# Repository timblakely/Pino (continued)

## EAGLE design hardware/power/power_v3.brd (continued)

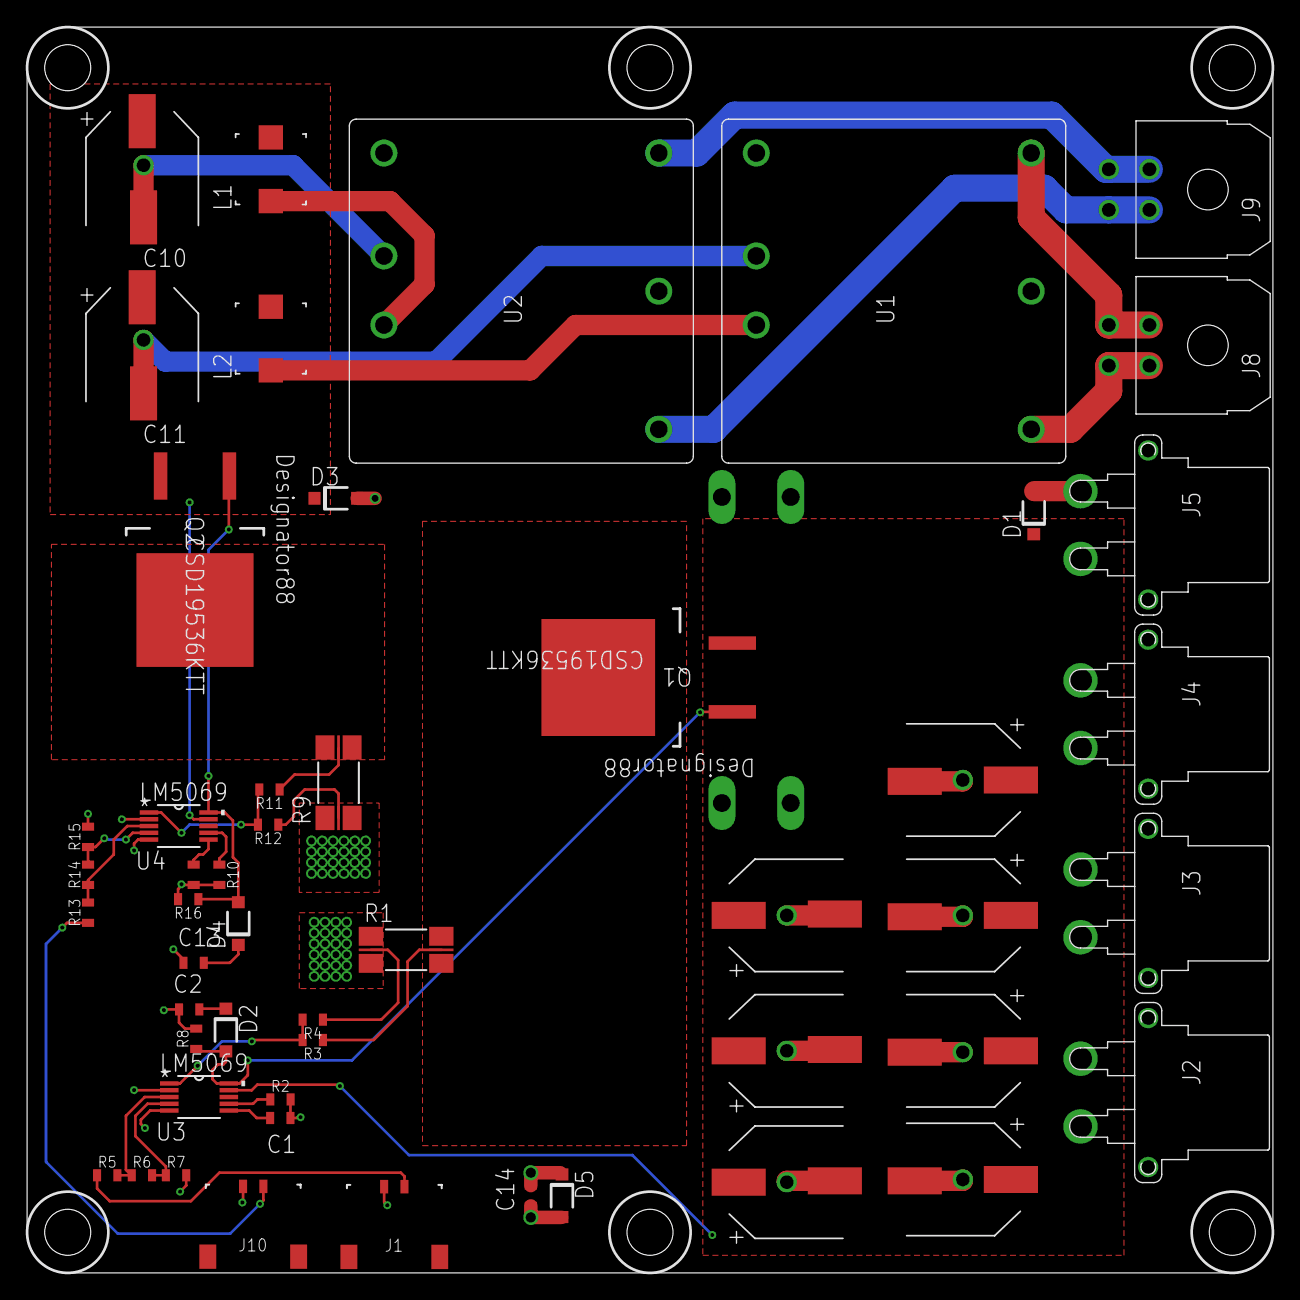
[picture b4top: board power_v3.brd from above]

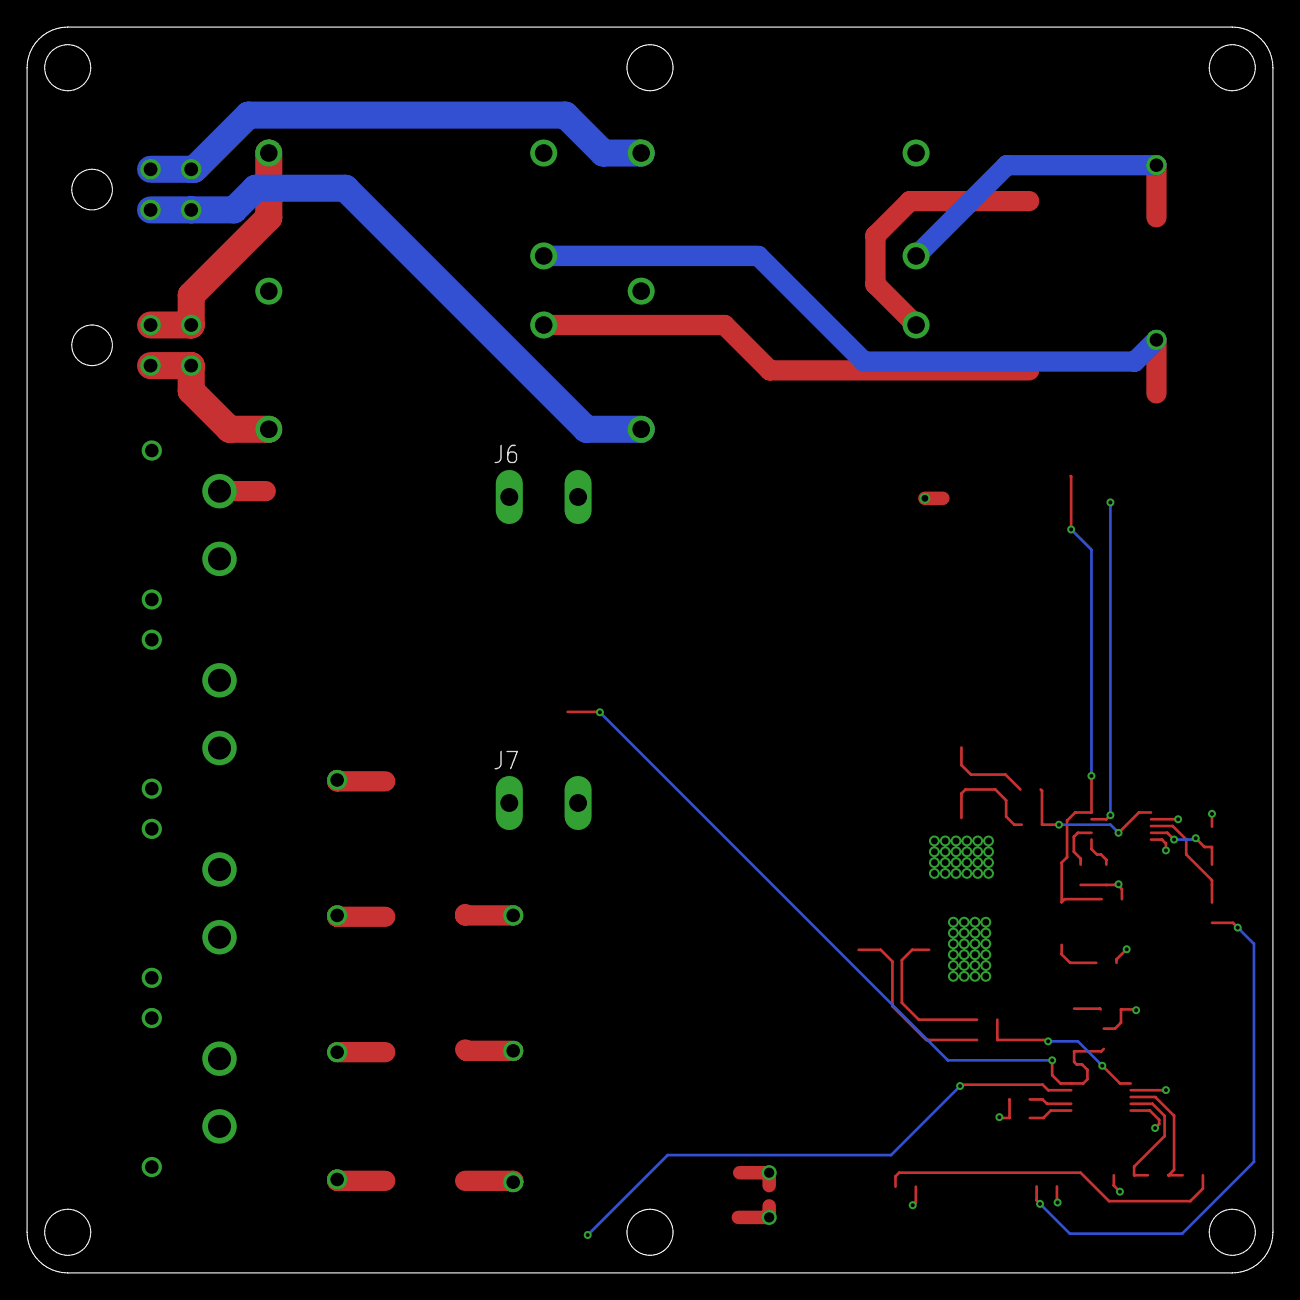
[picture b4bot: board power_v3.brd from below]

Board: 4 copper layers, 92.0 x 92.0 mm, 53 parts (2 on the bottom side), 32 nets.

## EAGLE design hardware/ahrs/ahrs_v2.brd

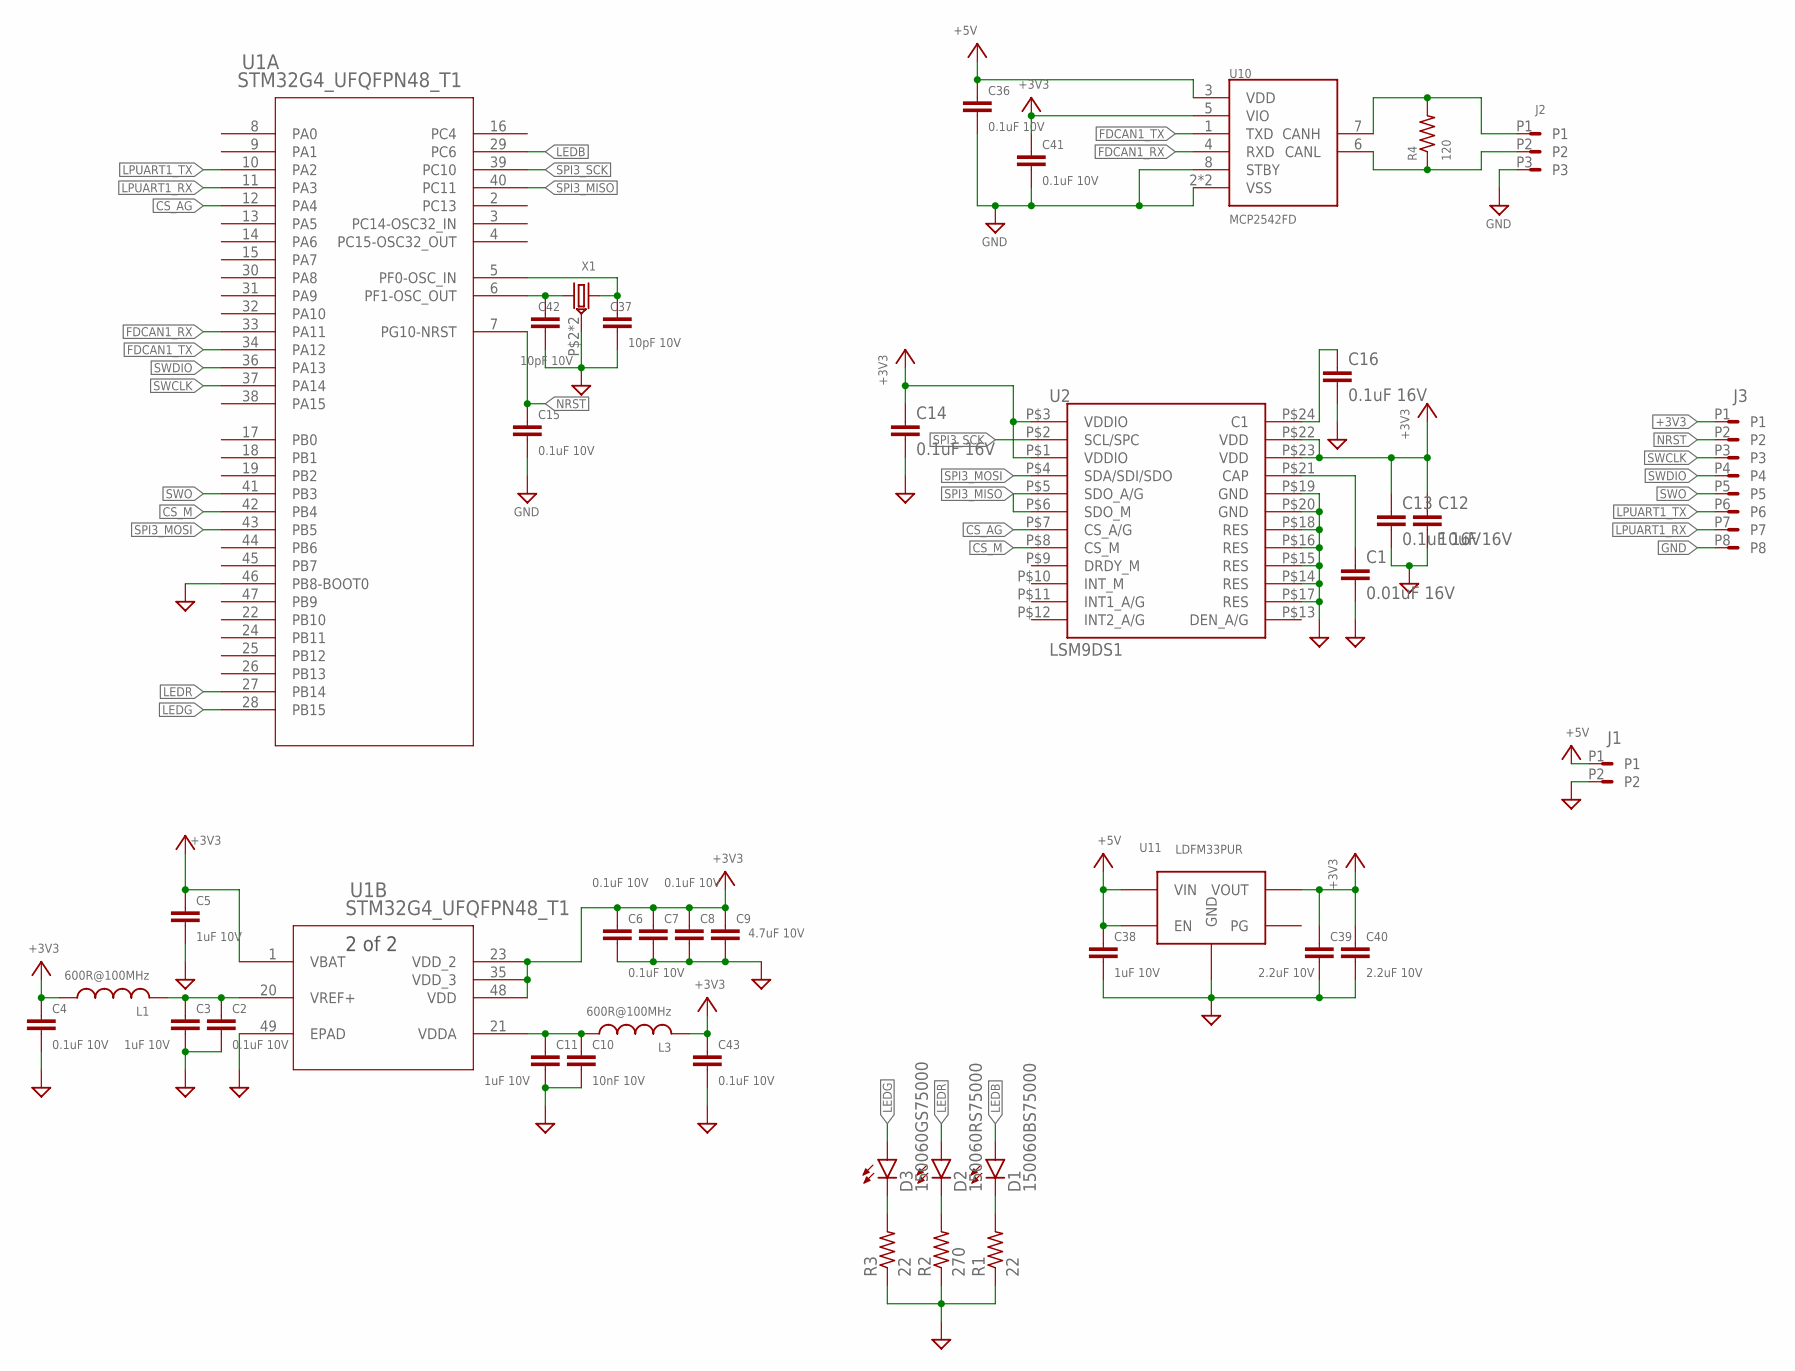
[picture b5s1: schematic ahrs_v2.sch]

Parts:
C1: 0.01uF 16V; C0603
C2, C4, C6, C7, C8, C15, C36, C41, C43: 0.1uF 10V; C0603
C3, C5, C11, C38: 1uF 10V; C0603
C9: 4.7uF 10V; C0603
C10: 10nF 10V; C0603
C12: 10uF 16V; C0603
C13, C14, C16: 0.1uF 16V; C0603
C37, C42: 10pF 10V; C0603
C39, C40: 2.2uF 10V; C0603
D1: 150060BS75000; D0603
D2: 150060RS75000; D0603
D3: 150060GS75000; D0603
J1: LINEAR_2_5040500291; MOLEX_5040500291
J2: LINEAR_35040500391; MOLEX_5040500391
J3: LINEAR_85040500891; MOLEX_5040500891
L1, L3: 600R@100MHz; L0603
R1, R3: 22; R0603
R2: 270; R0603
R4: 120; R0603
U1: STM32G4_UFQFPN48_T1; UFQFPN-48_7X7X0P55MM
U2: LSM9DS1; LGA24_3.5X3X1
U10: MCP2542FD; TDFN_2X3
U11: LDFM33PUR; DFN6_2X2
X1: CRYSTAL_NX2016SA-24MHZ-EXS00A-CS11335; NX201SA

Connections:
+3V3: C4.1, C5.1, C6.1, C7.1, C8.1, C9.1, C12.1, C13.1, C14.1, C39.1, C40.1, C41.1, C43.1, J3.P1, L1.1, L3.2, U1.1 (VBAT), U1.23 (VDD_2), U1.35 (VDD_3), U1.48 (VDD), U2.P$1 (VDDIO), U2.P$3 (VDDIO), U2.P$22 (VDD), U2.P$23 (VDD), U10.5 (VIO), U11.PIN1 (VOUT)
+5V: C36.1, C38.1, J1.P1, U10.3 (VDD), U11.PIN5 (EN), U11.PIN6 (VIN); also elsewhere on the board
CS_AG: U1.12 (PA4), U2.P$7 (CS_A/G)
CS_M: U1.42 (PB4), U2.P$8 (CS_M)
FDCAN1_RX: U1.33 (PA11), U10.4 (RXD)
FDCAN1_TX: U1.34 (PA12), U10.1 (TXD)
GND: C1.2, C2.2, C3.2, C4.2, C5.2, C6.2, C7.2, C8.2, C9.2, C10.2, C11.2, C12.2, C13.2, C14.2, C15.2, C16.2, C36.2, C37.2, C38.2, C39.2, C40.2, C41.2, C42.2, C43.2, J1.P2, J2.P3, J3.P8, R1.1, R2.1, R3.1, U1.46 (PB8-BOOT0), U1.49 (EPAD), U2.P$14 (RES), U2.P$15 (RES), U2.P$16 (RES), U2.P$17 (RES), U2.P$18 (RES), U2.P$19 (GND), U2.P$20 (GND), U10.2 (VSS), U10.8 (STBY), U10.PAD (VSS), U11.PAD (GND), U11.PIN4 (GND), X1.P$2 (GND), X1.P$4 (GND); also elsewhere on the board
LEDB: D1.2 (A), U1.29 (PC6)
LEDG: D3.2 (A), U1.28 (PB15)
LEDR: D2.2 (A), U1.27 (PB14)
LPUART1_RX: J3.P7, U1.11 (PA3)
LPUART1_TX: J3.P6, U1.10 (PA2)
unnamed: C2.1, C3.1, L1.2, U1.20 (VREF+)
unnamed: C37.1, U1.5 (PF0-OSC_IN), X1.P$3 (2)
unnamed: C42.1, U1.6 (PF1-OSC_OUT), X1.P$1 (1)
unnamed: C1.1, U2.P$21 (CAP)
unnamed: C16.1, U2.P$24 (C1)
unnamed: D3.1 (C), R3.2
unnamed: D2.1 (C), R2.2
unnamed: D1.1 (C), R1.2
unnamed: J2.P1, R4.2, U10.7 (CANH)
unnamed: J2.P2, R4.1, U10.6 (CANL)
unnamed: C10.1, C11.1, L3.1, U1.21 (VDDA)
NRST: C15.1, J3.P2, U1.7 (PG10-NRST)
SPI3_MISO: U1.40 (PC11), U2.P$5 (SDO_A/G), U2.P$6 (SDO_M)
SPI3_MOSI: U1.43 (PB5), U2.P$4 (SDA/SDI/SDO)
SPI3_SCK: U1.39 (PC10), U2.P$2 (SCL/SPC)
SWCLK: J3.P3, U1.37 (PA14)
SWDIO: J3.P4, U1.36 (PA13)
SWO: J3.P5, U1.41 (PB3)

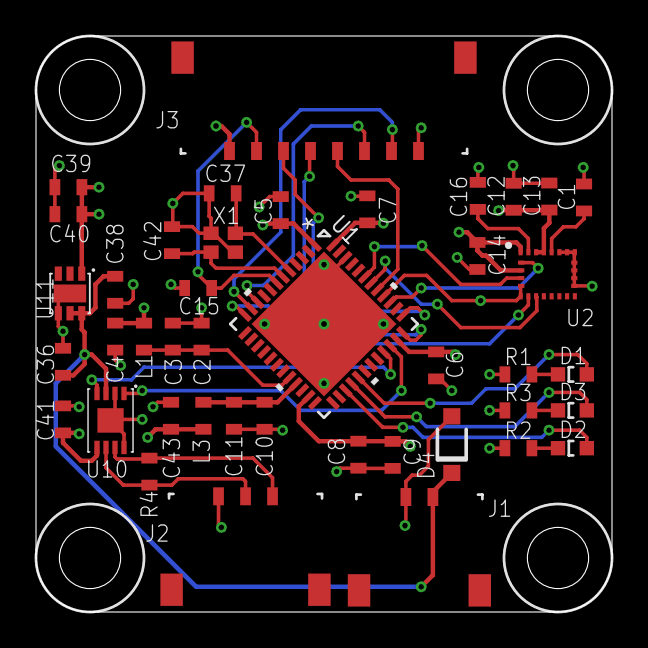
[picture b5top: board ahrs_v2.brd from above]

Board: 4 copper layers, 32.0 x 32.0 mm, 42 parts (0 on the bottom side), 30 nets.

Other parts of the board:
D4: SOD123

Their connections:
+5V: D4.C; also elsewhere on the board
GND: D4.A; also elsewhere on the board

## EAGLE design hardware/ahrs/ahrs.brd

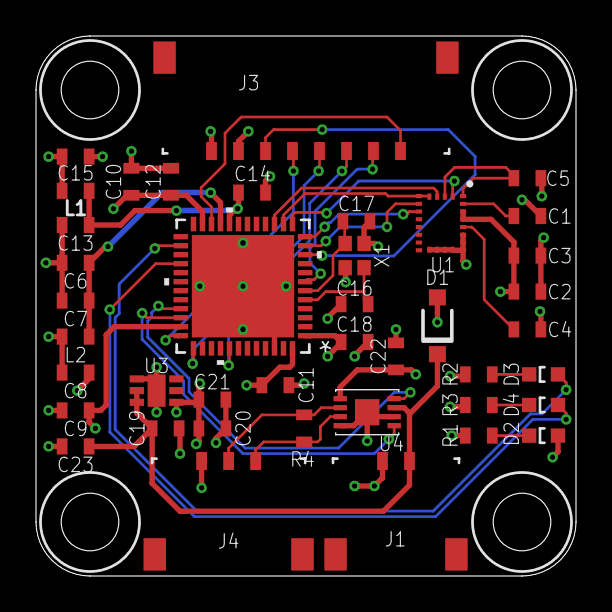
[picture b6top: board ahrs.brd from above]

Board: 4 copper layers, 30.0 x 30.0 mm, 41 parts (0 on the bottom side), 30 nets.

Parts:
C1, C3, C5, C6, C8, C9, C10, C13, C15: 0.1uF 10V; C0603
C2: 10uF 10v; C0603
C4: 10nF 16v; C0603
C7, C14, C18, C19: 1uF 10v; C0603
C11: 100nF 10v; C0603
C12: 4.7uF 10v; C0603
C16, C17: 10pF 10v; C0603
C20, C21: 2.2uF 10V; C0603
C22, C23: 0.1uF 10v; C0603
D1: SOD123
D2, D3, D4: 150060BS75000; D0603
J1: LINEAR_2_5040500291; MOLEX_5040500291
J3: LINEAR_85040500891; MOLEX_5040500891
J4: LINEAR_35040500391; MOLEX_5040500391
L1, L2: 600R@100MHz; L0603
R1, R2, R3: 22; R0603
R4: R0603
U1: LSM9DS1; LGA24_3.5X3X1
U2: STM32G4_UFQFPN48_T1; UFQFPN-48_7X7X0P55MM
U3: LDFM33PUR; DFN6_2X2
U4: MCP2542FD; TDFN_2X3
X1: CRYSTAL_NX2016SA-24MHZ-EXS00A-CS11335; NX201SA

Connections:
+3V3: C2.1, C3.1, C5.1, C8.1, C9.1, C10.1, C11.1, C12.1, C15.1, C18.1, C20.1, C21.1, C22.1, D2.2, J3.P1, L1.1, L2.2, U1.P$22, U1.P$23, U2.1, U2.23, U2.35, U2.48, U3.PIN1, U4.5
+5V: C19.1, C23.1, D1.C, J1.P1, U3.PIN5, U3.PIN6, U4.3
CAN_RX: U2.33, U4.4
CAN_TX: U2.34, U4.1
CS_AG: U1.P$7, U2.11
CS_M: U1.P$8, U2.12
GND: C1.1, C2.2, C3.2, C4.1, C6.2, C7.2, C8.2, C9.2, C10.2, C11.2, C12.2, C13.2, C14.2, C15.2, C16.2, C17.2, C18.2, C19.2, C20.2, C21.2, C22.2, C23.2, D1.A, J1.P2, J3.P2, J4.P3, R1.1, R2.2, R3.2, U1.P$14, U1.P$15, U1.P$16, U1.P$17, U1.P$18, U1.P$19, U1.P$20, U2.46, U2.49, U3.PAD, U3.PIN4, U4.2, U4.8, U4.PAD, X1.P$2, X1.P$4
LPUART_RX: J3.P8, U2.22
LPUART_TX: J3.P3, U2.10
MISO: U1.P$5, U1.P$6, U2.14
MOSI: U1.P$4, U2.15
unnamed: D2.1, R1.2
unnamed: C1.2, U1.P$24
unnamed: C4.2, U1.P$21
unnamed: C5.2, U1.P$1, U1.P$3
unnamed: C17.1, U2.6, X1.P$1
unnamed: C16.1, U2.5, X1.P$3
unnamed: D4.2, U2.28
unnamed: D3.2, U2.26
unnamed: D3.1, R2.1
unnamed: D4.1, R3.1
unnamed: J4.P1, R4.2, U4.7
unnamed: J4.P2, R4.1, U4.6
NRST: J3.P7, U2.7
SCK: U1.P$2, U2.13
SWCLK: J3.P5, U2.37
SWDIO: J3.P4, U2.36
SWO: J3.P6, U2.41
VDDA: C6.1, C7.1, L2.1, U2.21
VREF: C13.1, C14.1, L1.2, U2.20

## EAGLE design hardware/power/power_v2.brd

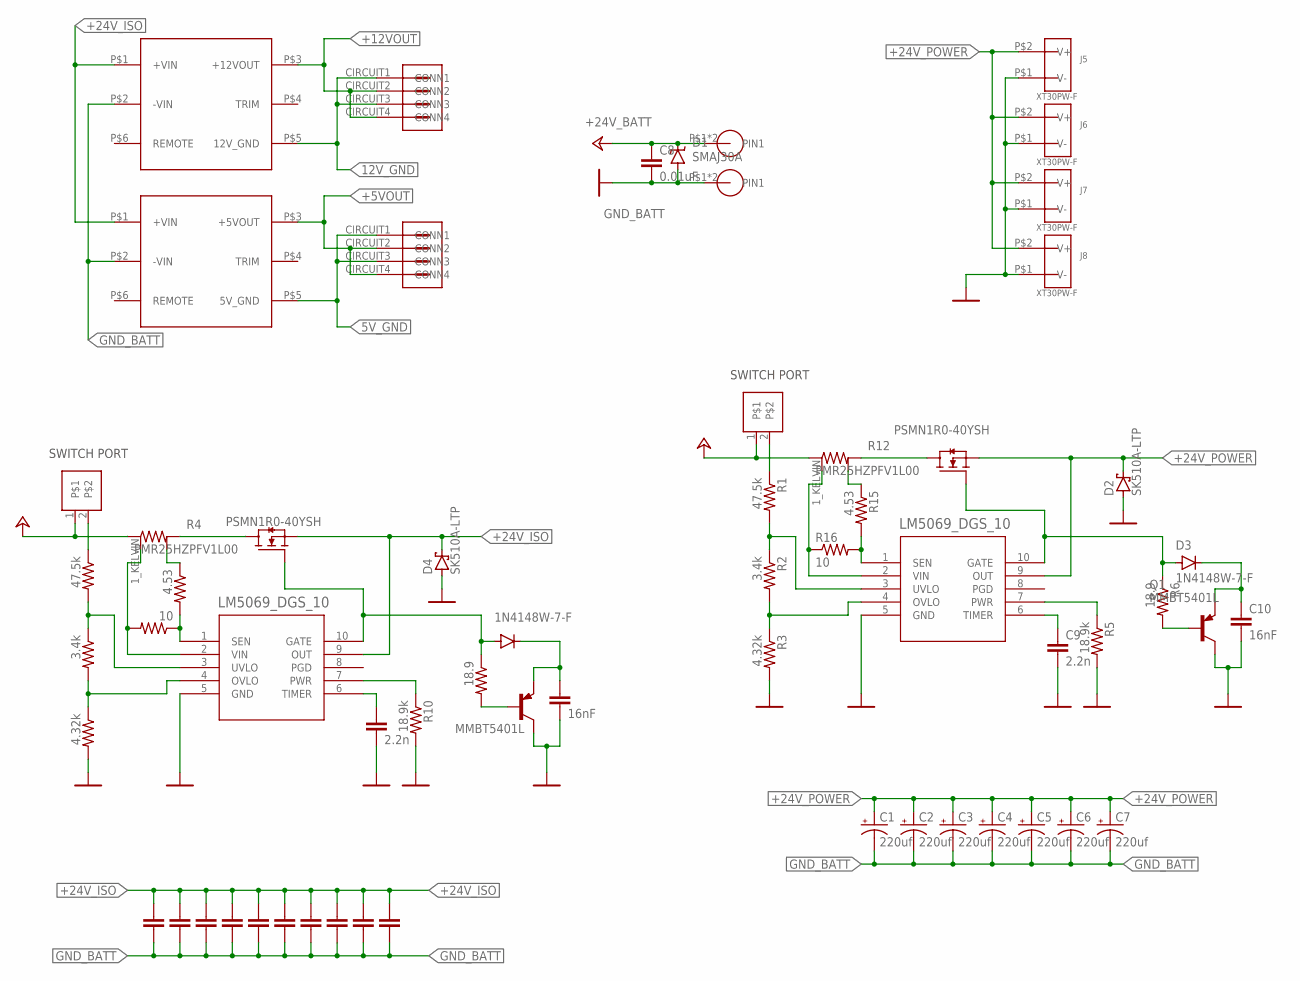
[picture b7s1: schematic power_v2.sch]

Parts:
C1, C2, C3, C4, C5, C6, C7: 220uf; C_ELEC_8X11_5
C8: 0.01uF; C1210
C9, C12: 2.2n; C1210
C10, C13: 16nF; C1210
C14, C15, C16, C17, C18, C19, C20, C21, C22, C23: 10uF; C1210
D1: SMAJ30A; DO-214AC
D2, D4: SK510A-LTP; DO-214AC
D3, D5: 1N4148W-7-F; SOD123
J1, J2: FASTON1289_ST; FASTON_1289-ST
J3: 12v; MOLEX_4_RA
J4: 5v; MOLEX_4_RA
J5, J6, J7, J8: XT30PW-F
Q1, Q3: MMBT5401L; SOT23-3
Q2, Q4: PSMN1R0-40YSH; LFPAK56E
R1, R7: 47.5k; R0603
R2, R8: 3.4k; R0603
R3, R9: 4.32k; R0603
R4, R12: PMR25HZPFV1L00; R1210_KELVIN
R5, R10: 18.9k; R0603
R6, R11: 18.9; R0603
R13, R16: 10; R0603
R14, R15: 4.53; R0603
U1: PDQ30-Q24-S5-D; PDQ30-D
U2: PDQ30-Q24-S12-D; PDQ30-D
U$1, U$14: LM5069_DGS_10; VSSOP_DGS_10
U$13, U$26: 2-PIN; M80-8420242

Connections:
5V_GND: J4.CIRCUIT1 (CONN1), J4.CIRCUIT3 (CONN3), U1.P$5 (5V_GND)
12V_GND: J3.CIRCUIT1 (CONN1), J3.CIRCUIT3 (CONN3), U2.P$5 (12V_GND)
+5VOUT: J4.CIRCUIT2 (CONN2), J4.CIRCUIT4 (CONN4), U1.P$3 (+5VOUT)
+12VOUT: J3.CIRCUIT2 (CONN2), J3.CIRCUIT4 (CONN4), U2.P$3 (+12VOUT)
+24V_BATT: C8.1, D1.C, J1.P$1, J1.P$2, R4.1A (1), R4.1B (1), R12.1A (1), R12.1B (1), U$13.1, U$26.1
+24V_ISO: C14.1, C15.1, C16.1, C17.1, C18.1, C19.1, C20.1, C21.1, C22.1, C23.1, D4.C, Q4.1 (S), Q4.2 (S), Q4.3 (S), U1.P$1 (+VIN), U2.P$1 (+VIN), U$14.9 (OUT)
+24V_POWER: C1.1 (+), C2.1 (+), C3.1 (+), C4.1 (+), C5.1 (+), C6.1 (+), C7.1 (+), D2.C, J5.P$2 (V+), J6.P$2 (V+), J7.P$2 (V+), J8.P$2 (V+), Q2.1 (S), Q2.2 (S), Q2.3 (S), U$1.9 (OUT)
GND_BATT: C1.2 (-), C2.2 (-), C3.2 (-), C4.2 (-), C5.2 (-), C6.2 (-), C7.2 (-), C8.2, C9.2, C10.2, C12.2, C13.2, C14.2, C15.2, C16.2, C17.2, C18.2, C19.2, C20.2, C21.2, C22.2, C23.2, D1.A, D2.A, D4.A, J2.P$1, J2.P$2, J5.P$1 (V-), J6.P$1 (V-), J7.P$1 (V-), J8.P$1 (V-), Q1.C, Q3.C, R3.2, R5.2, R9.2, R10.2, U1.P$2 (-VIN), U2.P$2 (-VIN), U$1.5 (GND), U$14.5 (GND)
MOSFET_DRAIN: Q2.5 (D), R12.2A (2), R12.2B (2)
MOSFET_DRAIN1: Q4.5 (D), R4.2A (2), R4.2B (2)
unnamed: R1.2, R2.1, U$1.3 (UVLO)
unnamed: R2.2, R3.1, U$1.4 (OVLO)
unnamed: R1.1, U$26.2
unnamed: R7.2, R8.1, U$14.3 (UVLO)
unnamed: D3.A, Q2.4 (G), R6.1, U$1.10 (GATE)
unnamed: R5.1, U$1.7 (PWR)
unnamed: C9.1, U$1.6 (TIMER)
unnamed: C10.1, D3.C, Q1.E
unnamed: Q1.B, R6.2
unnamed: R15.2, R16.2, U$1.1 (SEN)
unnamed: R12.2_KELVIN (2K), R15.1
unnamed: R8.2, R9.1, U$14.4 (OVLO)
unnamed: R7.1, U$13.2
unnamed: D5.A, Q4.4 (G), R11.1, U$14.10 (GATE)
unnamed: R10.1, U$14.7 (PWR)
unnamed: C12.1, U$14.6 (TIMER)
unnamed: C13.1, D5.C, Q3.E
unnamed: Q3.B, R11.2
unnamed: R12.1_KELVIN (1K), R16.1, U$1.2 (VIN)
unnamed: R13.1, R14.2, U$14.1 (SEN)
unnamed: R4.2_KELVIN (2K), R14.1
unnamed: R4.1_KELVIN (1K), R13.2, U$14.2 (VIN)

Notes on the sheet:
SWITCH PORT

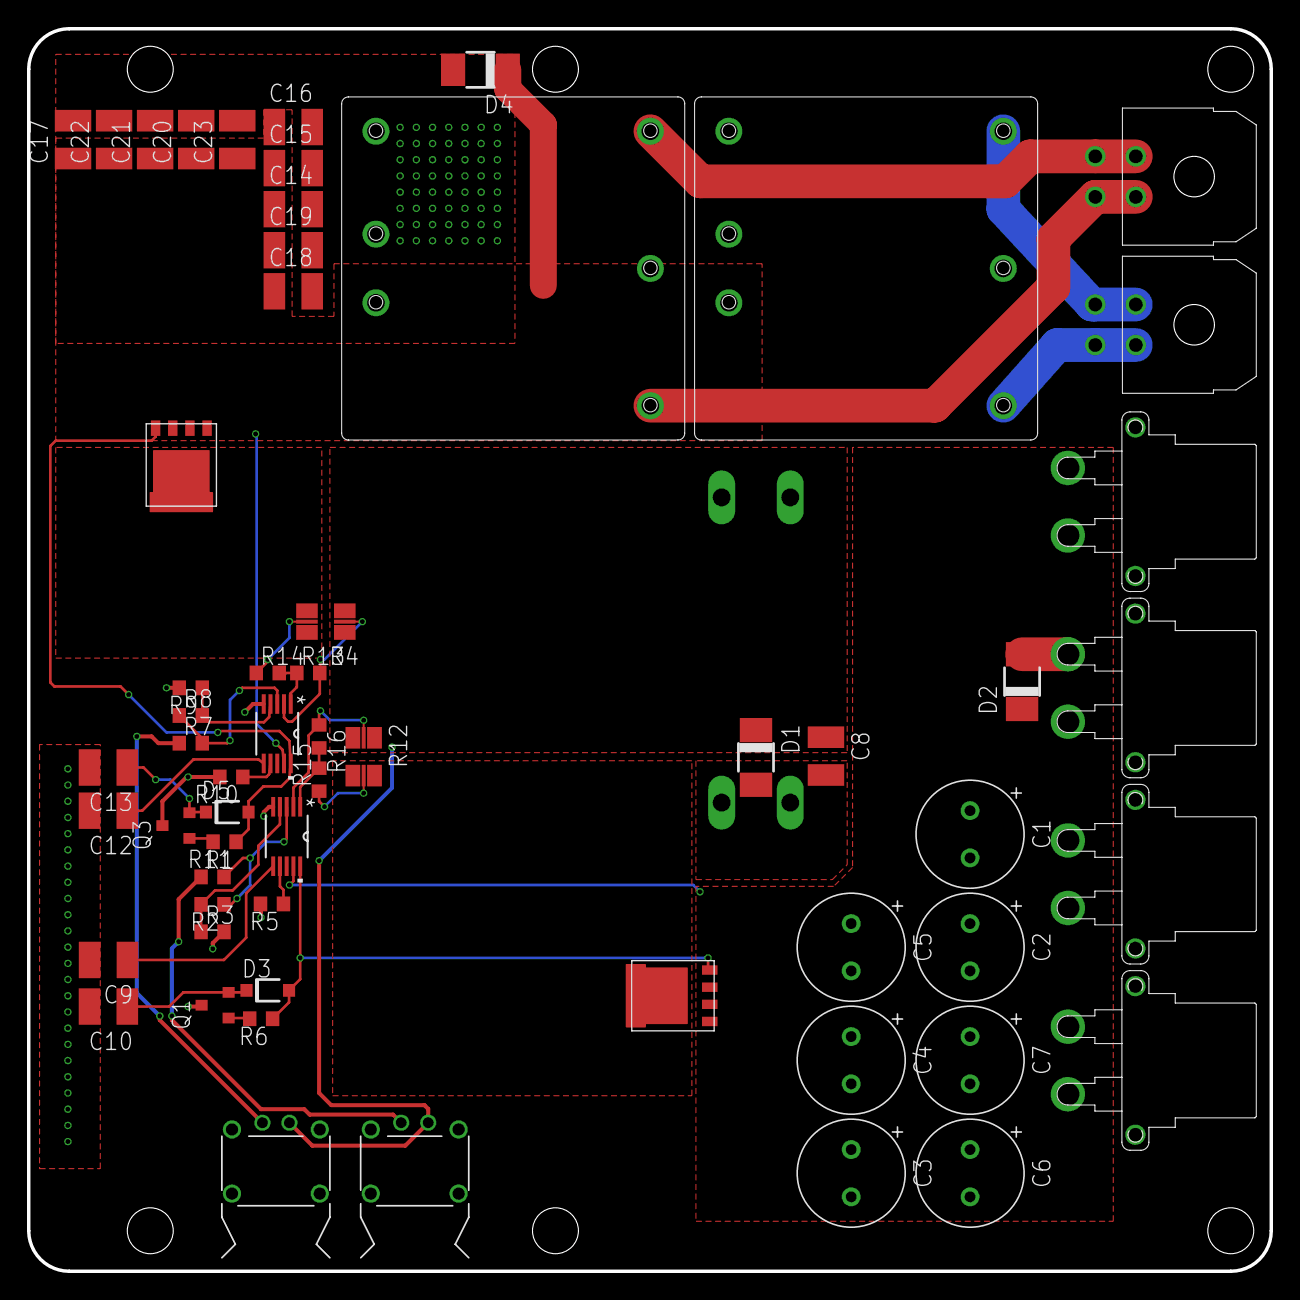
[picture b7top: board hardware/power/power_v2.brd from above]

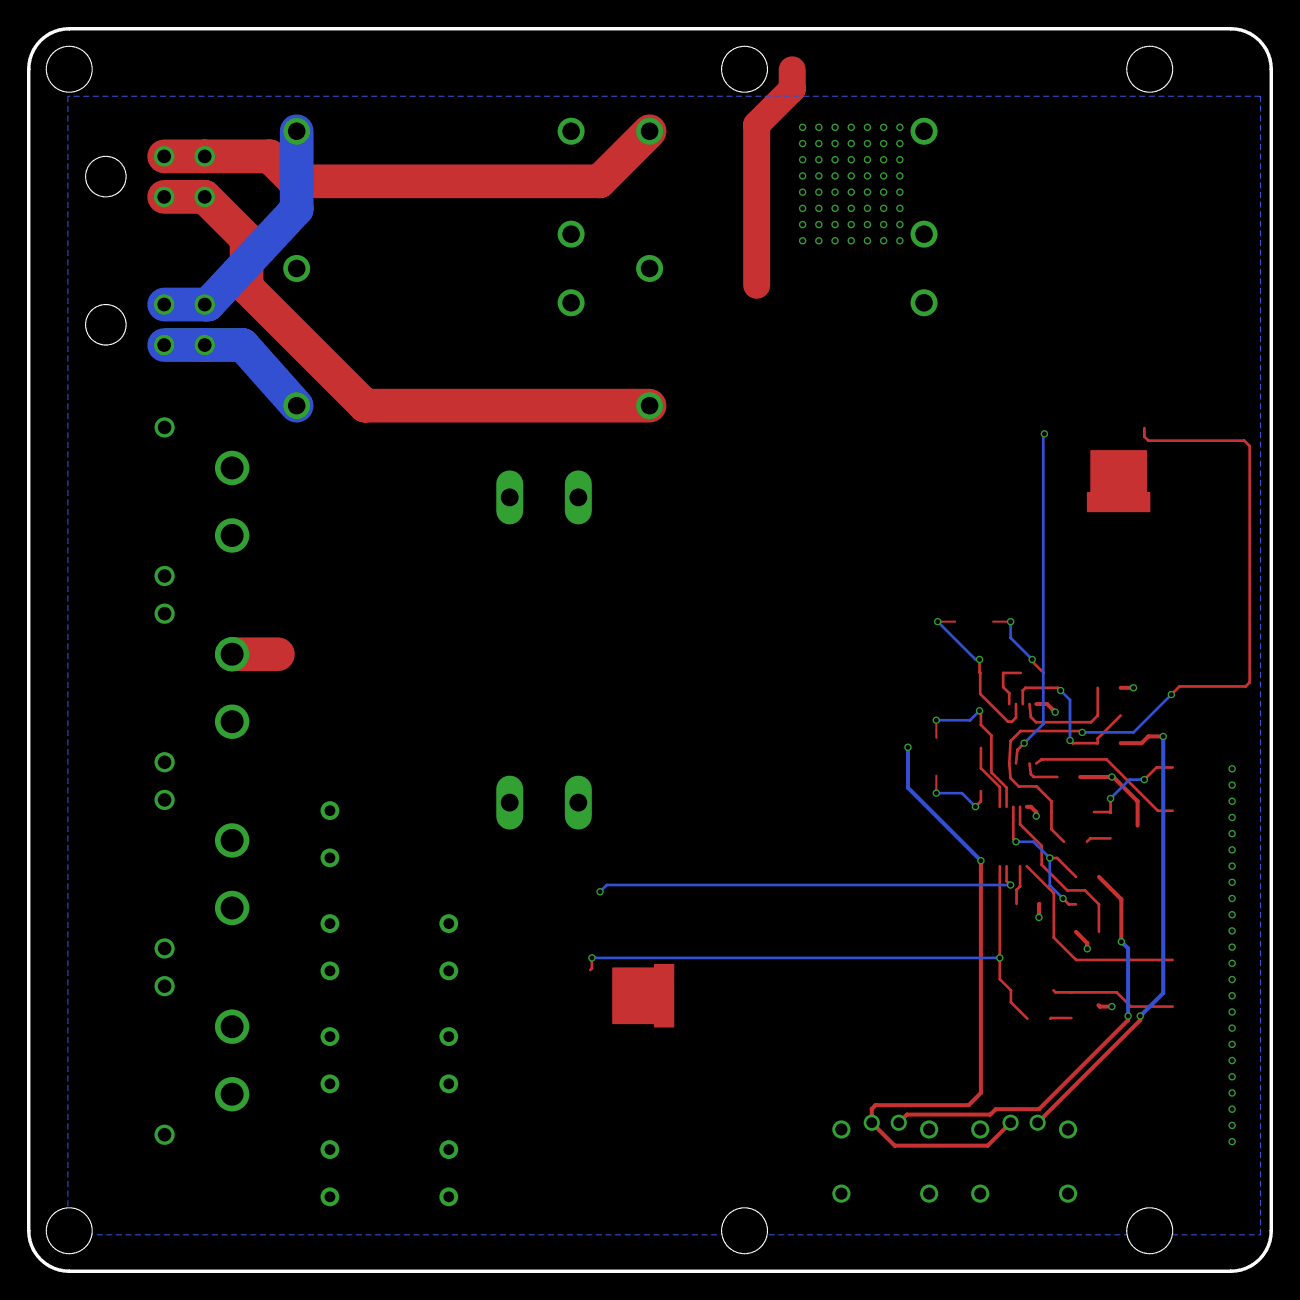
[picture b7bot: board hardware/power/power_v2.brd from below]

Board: 2 copper layers, 92.0 x 92.0 mm, 61 parts (2 on the bottom side), 32 nets.

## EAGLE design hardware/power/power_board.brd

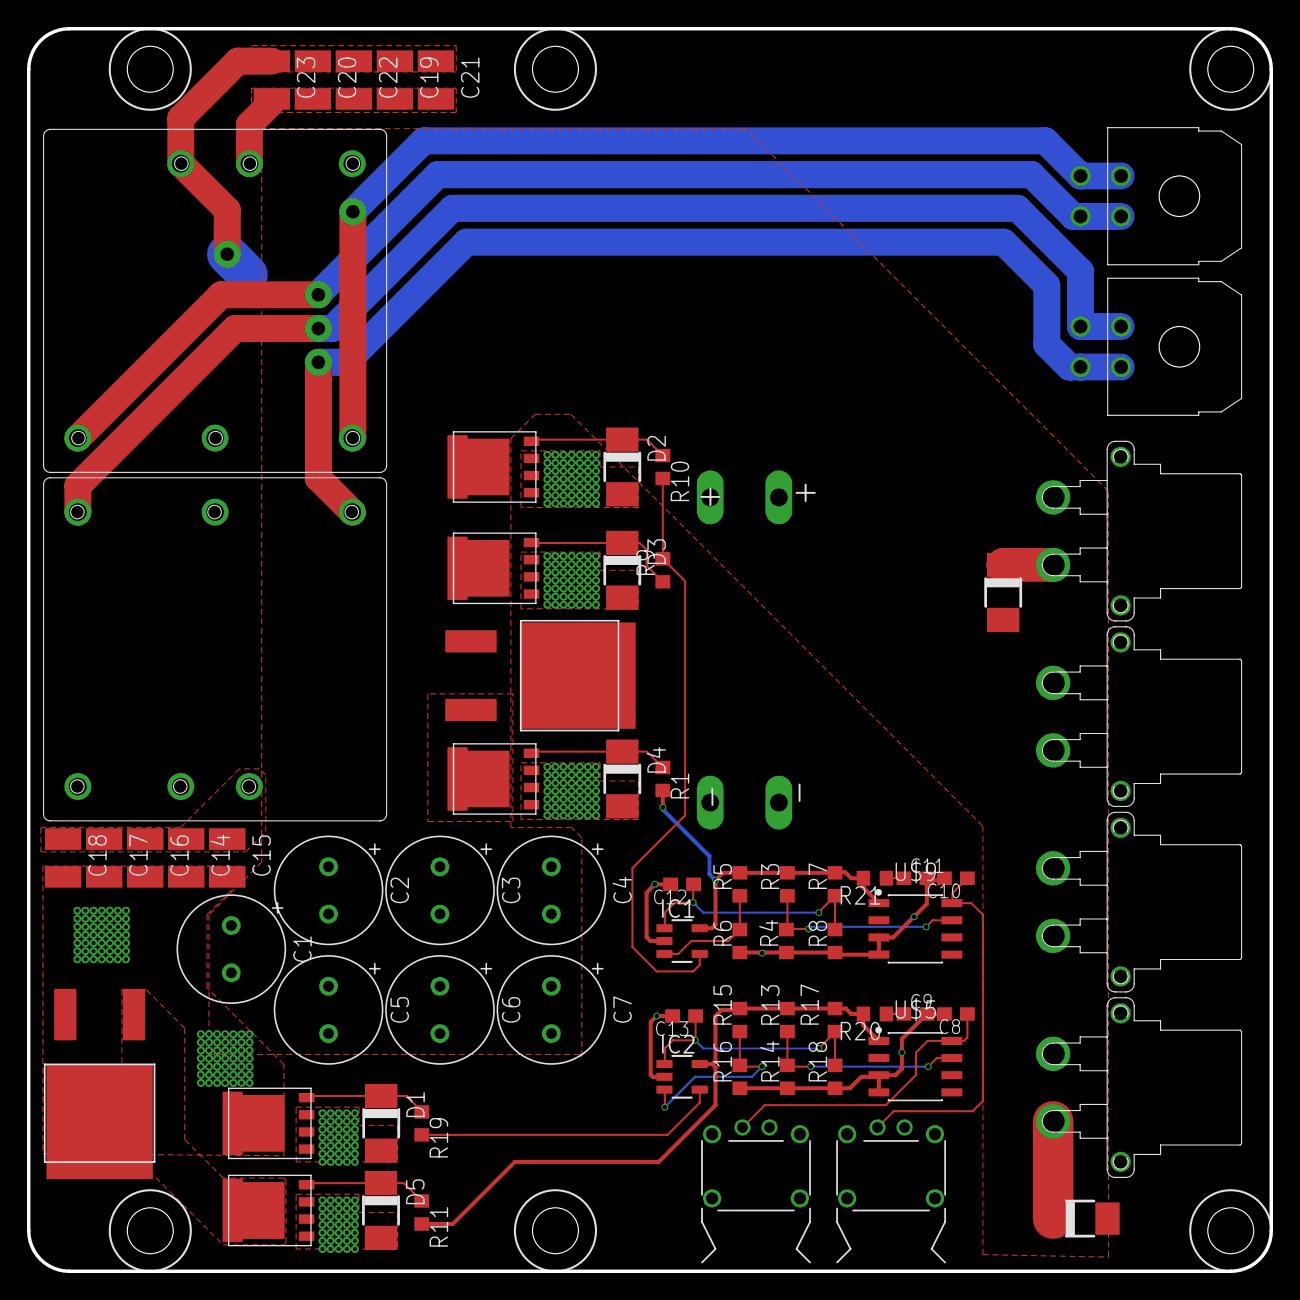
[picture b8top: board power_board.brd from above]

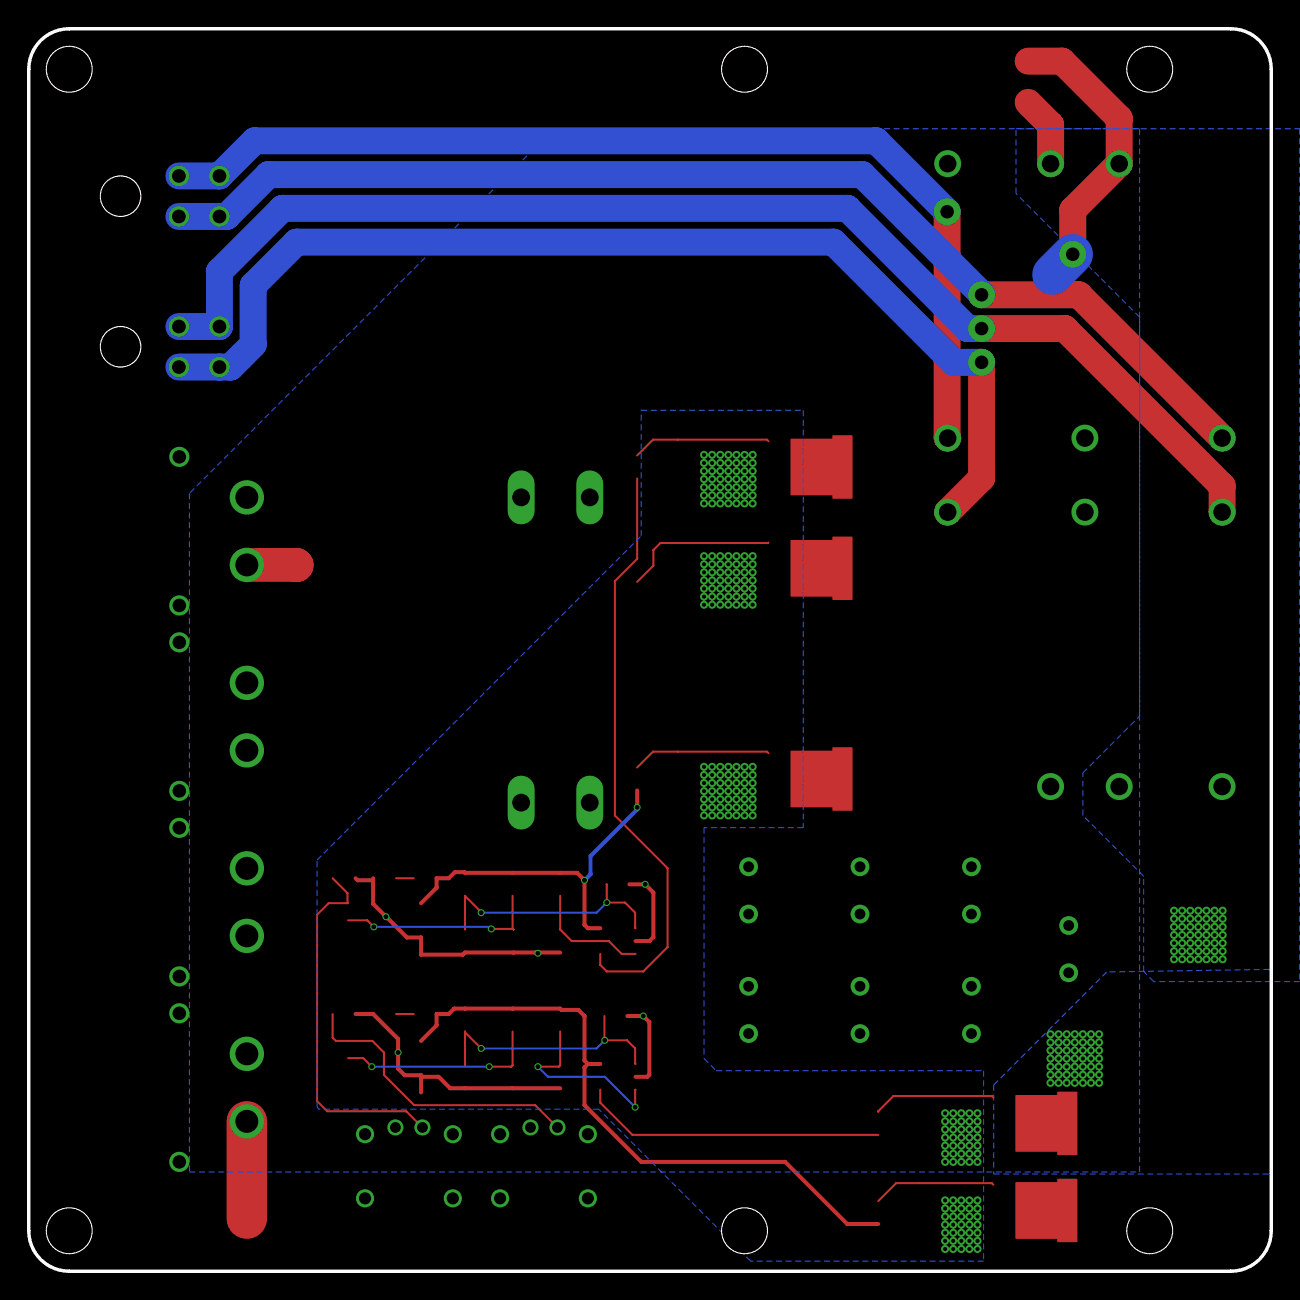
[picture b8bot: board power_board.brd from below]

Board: 2 copper layers, 92.0 x 92.0 mm, 72 parts (2 on the bottom side), 29 nets.

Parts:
C1, C2, C3, C4, C5, C6, C7: 220uf; C_ELEC_8X11_5
C8, C9, C10, C11: 2.2uF; C0603
C12, C13: 300nF; C0603
C14, C15, C16, C17, C18, C19, C20, C21, C22, C23: 10uF; C1210
D1, D2, D3, D4, D5: SMAJ12A; DO-214AC
D6, D7: SK510A-LTP; DO-214AC
IC1, IC2: LM321MF; SOT23-5
J1, J2: FASTON1289_ST; FASTON_1289-ST
J3: 12v; MOLEX_4_RA
J4: 5v; MOLEX_4_RA
J5, J6, J7, J8: XT30PW-F
R1, R9, R10, R11, R19: 4.7k; R0603
R2, R12: 2; PWR163
R3, R13: 873.1k; R0603
R4, R14: 100k; R0603
R5, R7, R15, R17: 100k\; R0603
R6, R16: 400k; R0603
R8, R18: 500k; R0603
R20, R21: 0.5; R0603
U1: PDQ30-Q24-S5-D; PDQ30-D
U2: PDQ30-Q24-S12-D; PDQ30-D
U$1, U$2, U$3, U$6, U$11: PSMN1R0-40YSH; LFPAK56E
U$5, U$9: LP2951ACMM/NOPB; LP2591
U$26, U$27: 2-PIN; M80-8420242

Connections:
5V_GND: J4.CIRCUIT1, J4.CIRCUIT3, U1.P$5
12V_GND: J3.CIRCUIT1, J3.CIRCUIT3, U2.P$5
+5VOUT: J4.CIRCUIT2, J4.CIRCUIT4, U1.P$3
+12VOUT: J3.CIRCUIT2, J3.CIRCUIT4, U2.P$3
BATT_+24V: C1.1, C2.1, C3.1, C4.1, C5.1, C6.1, C7.1, C14.1, C15.1, C16.1, C17.1, C18.1, C19.1, C20.1, C21.1, C22.1, C23.1, D6.C, D7.C, J1.P$1, J1.P$2, J5.P$2, J6.P$2, J7.P$2, J8.P$2, U1.P$1, U2.P$1, U$26.1, U$27.1
BATT_GND: C8.2, C9.2, C10.2, C11.2, C12.2, C13.2, D1.A, D2.A, D3.A, D4.A, D5.A, IC1.2, IC2.2, J2.P$1, J2.P$2, R4.1, R6.1, R8.1, R14.1, R16.1, R18.1, U$1.1, U$1.2, U$1.3, U$2.1, U$2.2, U$2.3, U$3.1, U$3.2, U$3.3, U$5.3, U$5.4, U$6.1, U$6.2, U$6.3, U$9.3, U$9.4, U$11.1, U$11.2, U$11.3
ISO_12V: IC2.5, R11.2, R13.2, R15.2, R17.2, R20.2, U$5.1
ISO_GND: C14.2, C15.2, C16.2, C17.2, C18.2, C19.2, C20.2, C21.2, C22.2, C23.2, R12.P$2, U1.P$2, U2.P$2, U$6.5
LEG_12V: IC1.5, R1.2, R3.2, R5.2, R7.2, R21.2, U$9.1
LEG_GND: C1.2, C2.2, C3.2, C4.2, C5.2, C6.2, C7.2, D6.A, D7.A, J5.P$1, J6.P$1, J7.P$1, J8.P$1, R2.P$1, U$1.5, U$2.5
unnamed: R2.P$2, U$11.5
unnamed: D4.C, R1.1, U$11.4
unnamed: R3.1, R4.2, U$9.7
unnamed: IC1.3, R5.1, R6.2
unnamed: C12.1, IC1.1, R7.1, R8.2
unnamed: IC1.4, R9.2, R10.2
unnamed: D5.C, R11.1, U$3.4
unnamed: D3.C, R9.1, U$1.4
unnamed: D2.C, R10.1, U$2.4
unnamed: R13.1, R14.2, U$5.7
unnamed: R12.P$1, U$3.5
unnamed: IC2.3, R15.1, R16.2
unnamed: C13.1, IC2.1, R17.1, R18.2
unnamed: IC2.4, R19.2
unnamed: D1.C, R19.1, U$6.4
unnamed: C9.1, R20.1
unnamed: C11.1, R21.1
unnamed: C8.1, U$5.8, U$26.2
unnamed: C10.1, U$9.8, U$27.2
